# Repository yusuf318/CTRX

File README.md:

# CTRX
Yeniay Control Telemetry Project

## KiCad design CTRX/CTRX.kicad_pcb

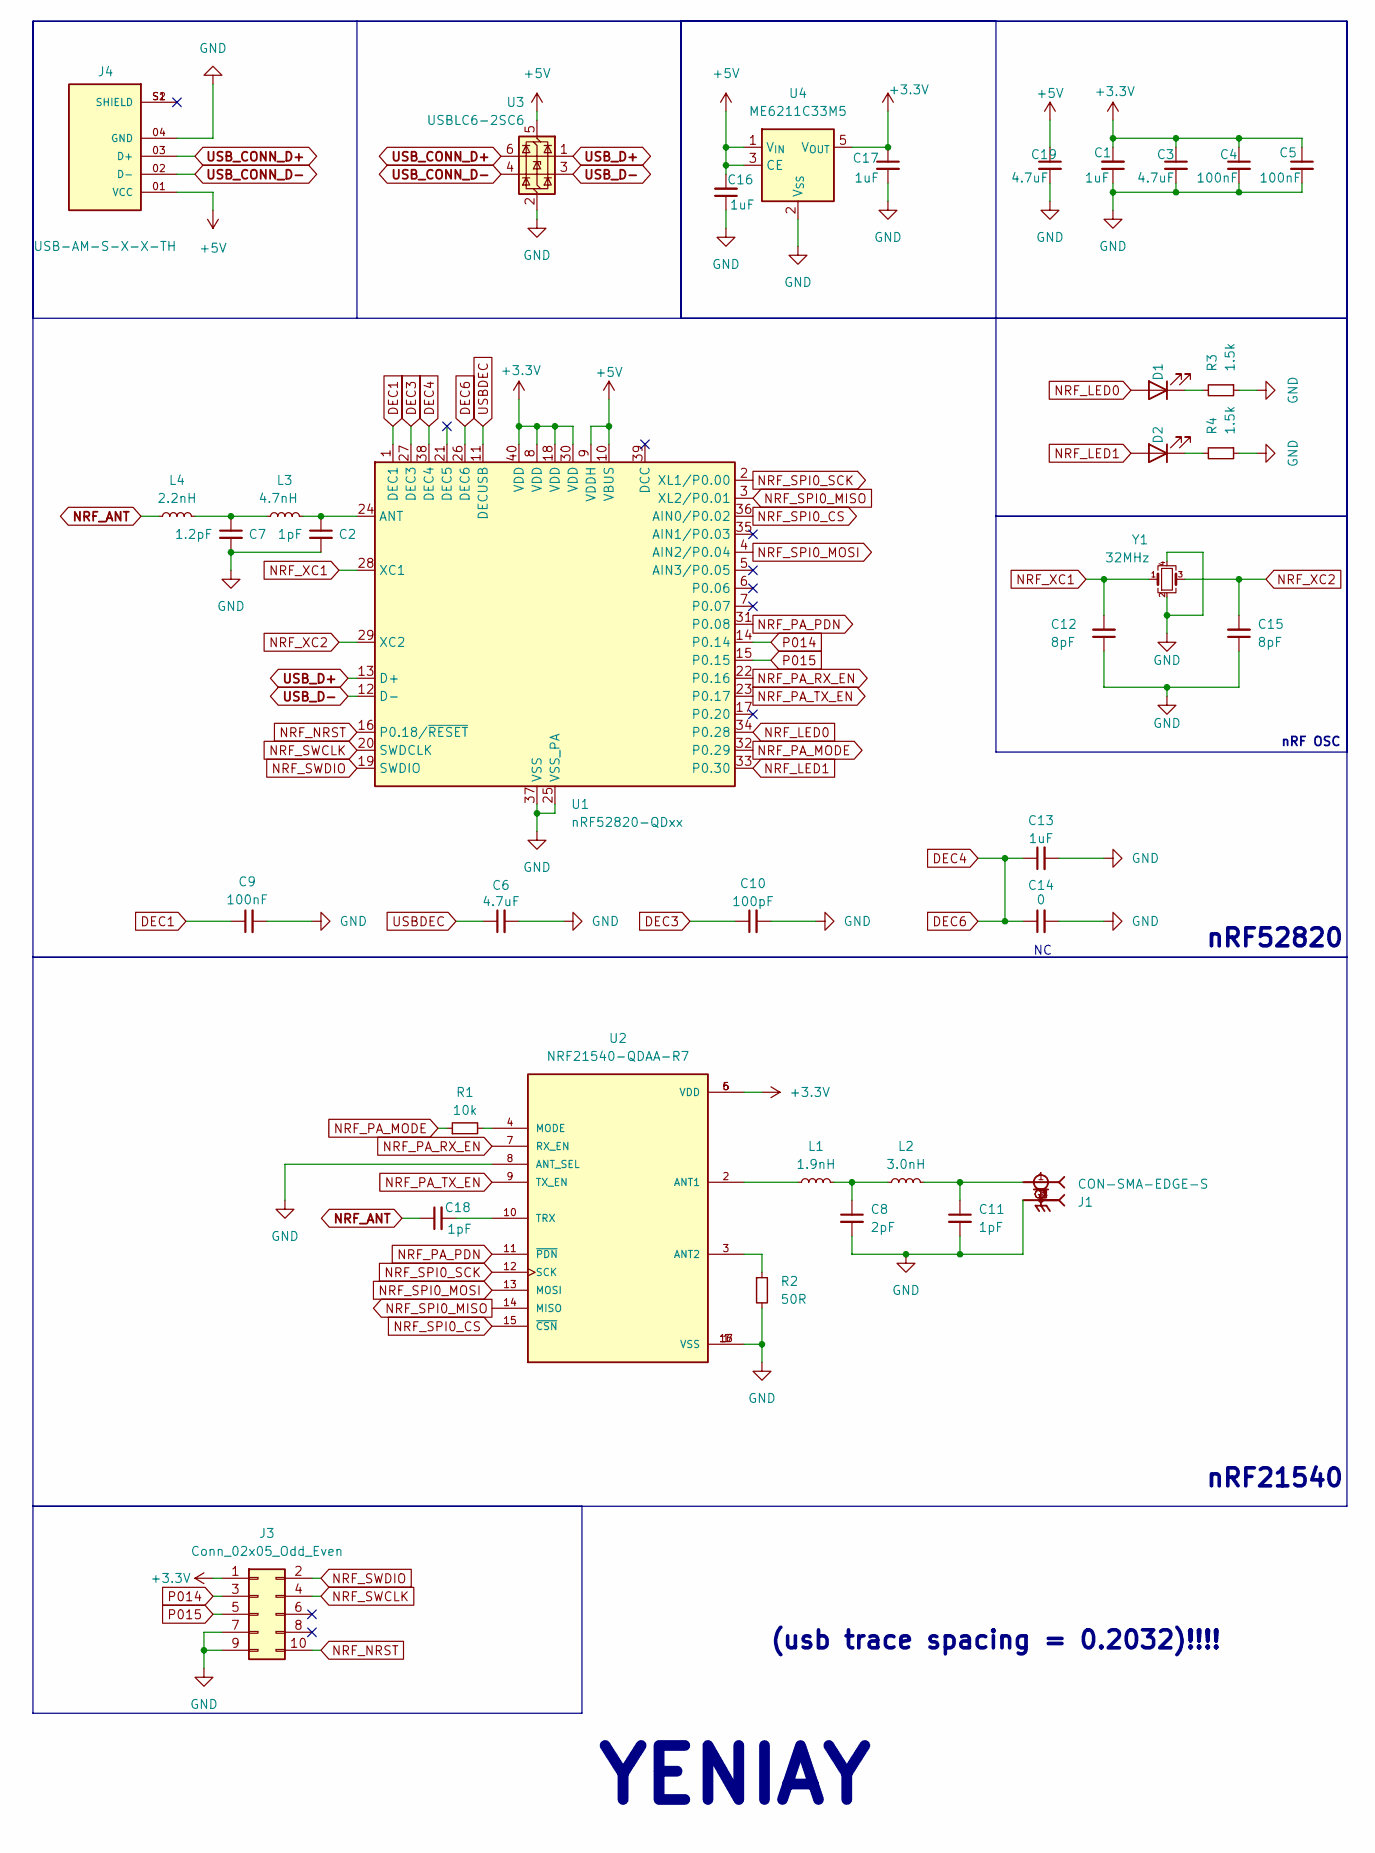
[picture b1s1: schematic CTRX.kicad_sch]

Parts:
C1, C13, C16, C17: 1uF; C_0402_1005Metric
C2, C11, C18: 1pF; C_0201_0603Metric
C3, C6, C19: 4.7uF; C_0603_1608Metric
C4, C5, C9: 100nF; C_0402_1005Metric
C7: 1.2pF; C_0201_0603Metric
C8: 2pF; C_0201_0603Metric
C10: 100pF; C_0402_1005Metric
C12, C15: 8pF; C_0402_1005Metric
C14: 0; C_0402_1005Metric
D1, D2: LED; LED_0805_2012Metric
J1: CON-SMA-EDGE-S; RFSOLUTIONS_CON-SMA-EDGE-S; PARTREV 1
J3: Conn_02x05_Odd_Even; IDC-Header_2x05_P2.54mm_Vertical
J4: USB-AM-S-X-X-TH; SAMTEC_USB-AM-S-X-X-TH; PARTREV U
L1: 1.9nH; L_0201_0603Metric
L2: 3.0nH; L_0201_0603Metric
L3: 4.7nH; L_0201_0603Metric
L4: 2.2nH; L_0201_0603Metric
R1: 10k; R_0402_1005Metric
R2: 50R; R_0402_1005Metric
R3, R4: 1.5k; R_0402_1005Metric
U1: nRF52820-QDxx; QFN-40-1EP_5x5mm_P0.4mm_EP3.6x3.6mm
U2: NRF21540-QDAA-R7; QFN65P400X400X95-17N; PARTREV 1.0
U3: USBLC6-2SC6; SOT-23-6
U4: ME6211C33M5; SOT-23-5
Y1: 32MHz; Crystal_SMD_3225-4Pin_3.2x2.5mm

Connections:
+3.3V: C1.2, C3.1, C4.1, C5.1, C17.1, J3.1, U1.8 (VDD), U1.18 (VDD), U1.30 (VDD), U1.40 (VDD), U2.5 (VDD), U2.6 (VDD), U4.5 (V_{OUT})
+5V: C16.2, C19.1, J4.01 (VCC), U1.9 (VDDH), U1.10 (VBUS), U3.5 (VBUS), U4.1 (V_{IN}), U4.3 (CE)
DEC1: C9.1, U1.1 (DEC1)
DEC3: C10.1, U1.27 (DEC3)
DEC4: C13.1, C14.1, U1.26 (DEC6), U1.38 (DEC4)
GND: C1.1, C2.2, C3.2, C4.2, C5.2, C6.2, C7.2, C8.2, C9.2, C10.2, C11.2, C12.1, C13.2, C14.2, C15.1, C16.1, C17.2, C19.2, J1.G1, J1.G2, J1.G3, J1.G4, J3.7, J3.9, J4.04 (GND), R2.2, R3.1, R4.1, U1.25 (VSS_PA), U1.37 (VSS), U1.41 (VSS), U2.1 (VSS), U2.8 (ANT_SEL), U2.16 (VSS), U2.17 (VSS), U3.2 (GND), U4.2 (V_{SS}), Y1.2, Y1.4
NRF_ANT: C18.1, L4.2
NRF_LED0: D1.2 (A), U1.34 (P0.28)
NRF_LED1: D2.2 (A), U1.33 (P0.30)
NRF_NRST: J3.10, U1.16 (P0.18/~RESET)
NRF_PA_MODE: R1.1, U1.32 (P0.29)
NRF_PA_PDN: U1.31 (P0.08), U2.11 (~PDN)
NRF_PA_RX_EN: U1.22 (P0.16), U2.7 (RX_EN)
NRF_PA_TX_EN: U1.23 (P0.17), U2.9 (TX_EN)
NRF_SPI0_CS: U1.36 (AIN0/P0.02), U2.15 (~CSN)
NRF_SPI0_MISO: U1.3 (XL2/P0.01), U2.14 (MISO)
NRF_SPI0_MOSI: U1.4 (AIN2/P0.04), U2.13 (MOSI)
NRF_SPI0_SCK: U1.2 (XL1/P0.00), U2.12 (SCK)
NRF_SWCLK: J3.4, U1.20 (SWDCLK)
NRF_SWDIO: J3.2, U1.19 (SWDIO)
NRF_XC1: C12.2, U1.28 (XC1), Y1.1
NRF_XC2: C15.2, U1.29 (XC2), Y1.3
unnamed: C7.1, L3.2, L4.1
unnamed: C8.1, L1.2, L2.1
unnamed: C11.1, J1.1, L2.2
unnamed: D1.1 (K), R3.2
unnamed: D2.1 (K), R4.2
unnamed: C2.1, L3.1, U1.24 (ANT)
unnamed: L1.1, U2.2 (ANT1)
unnamed: R2.1, U2.3 (ANT2)
unnamed: R1.2, U2.4 (MODE)
unnamed: C18.2, U2.10 (TRX)
P014: J3.3, U1.14 (P0.14)
P015: J3.5, U1.15 (P0.15)
USBDEC: C6.1, U1.11 (DECUSB)
USB_CONN_D+: J4.03 (D+), U3.6 (I/O1)
USB_CONN_D-: J4.02 (D-), U3.4 (I/O2)
USB_D+: U1.13 (D+), U3.1 (I/O1)
USB_D-: U1.12 (D-), U3.3 (I/O2)

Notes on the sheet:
nRF OSC
nRF21540
YENIAY
nRF52820
(usb trace spacing = 0.2032)!!!!

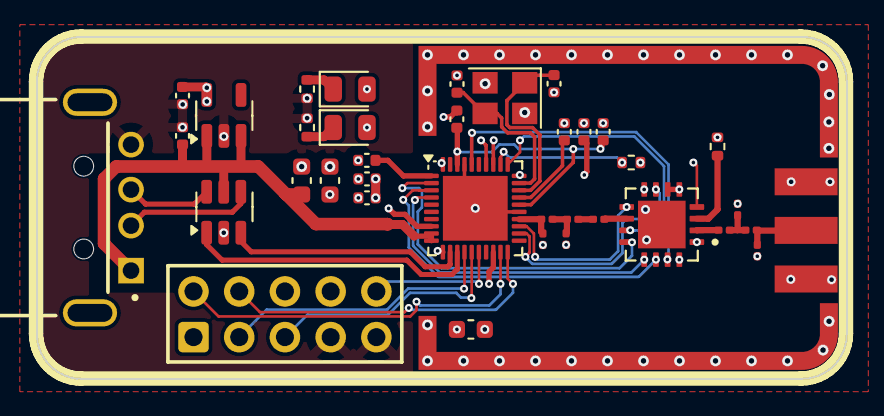
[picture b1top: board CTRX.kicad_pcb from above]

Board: 4 copper layers, 45.0 x 19.0 mm, 37 parts (0 on the bottom side), 39 nets.

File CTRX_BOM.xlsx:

Comment | Designator | Footprint | Part Number
1uF | C1, C13, C16, C17 | Capacitor_SMD:C_0402_1005Metric | C52923
1pF | C2, C11, C18 | Capacitor_SMD:C_0201_0603Metric | C88903
4.7uF | C3, C6, C19 | Capacitor_SMD:C_0603_1608Metric | C19666
100nF | C4, C5, C9 | Capacitor_SMD:C_0402_1005Metric | C1525
1.2pF | C7 | Capacitor_SMD:C_0201_0603Metric | C85895
2pF | C8 | Capacitor_SMD:C_0201_0603Metric | C505489
100pF | C10 | Capacitor_SMD:C_0402_1005Metric | C1546
8pF | C12, C15 | Capacitor_SMD:C_0402_1005Metric | C1864375
LED | D1 | LED_SMD:LED_0805_2012Metric | C2297
LED | D2 | LED_SMD:LED_0805_2012Metric | C2296
1.9nH | L1 | Inductor_SMD:L_0201_0603Metric | C206445
3.0nH | L2 | Inductor_SMD:L_0201_0603Metric | C86111
4.7nH | L3 | Inductor_SMD:L_0201_0603Metric | C86126
2.2nH | L4 | Inductor_SMD:L_0201_0603Metric | C1329438
10k | R1 | Resistor_SMD:R_0402_1005Metric | C25744
50R | R2 | Resistor_SMD:R_0402_1005Metric | C853312
1.5k | R3, R4 | Resistor_SMD:R_0402_1005Metric | C25867
nRF52820-QDxx | U1 | Package_DFN_QFN:QFN-40-1EP_5x5mm_P0.4mm_EP3.6x3.6mm | C3015612
NRF21540-QDAA-R7 | U2 | nRF21540:QFN65P400X400X95-17N | C5357827
USBLC6-2SC6 | U3 | Package_TO_SOT_SMD:SOT-23-6 | C7519
ME6211C33M5 | U4 | Package_TO_SOT_SMD:SOT-23-5 | C82942
32MHz | Y1 | Crystal:Crystal_SMD_3225-4Pin_3.2x2.5mm | C426985

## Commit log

2025-04-20 Start page settings.
2025-04-20 Selecting and adding component
2025-04-21 Scheme drawing.
2025-04-25 SPI3 pinleri kaldirildi, D+/D- baglantilari yapildi, NC pinler isaretlendi, C12/C15 12pF yapildi, dec kapasitorleri konumlandirildi, (2x5) debug connector ve ME6211 regulator eklendi.
2025-05-04 Pin baglantilari duzenlendi, C12/C15 12pF yapildi, nrf anten pinine 1 pF kapasitor eklendi, 2x5 debug connector ve regulator eklendi.
2025-05-09 schematic upgraded
2025-05-10 schematic updated
2025-05-11 dxf added.
2025-05-11 sma edge added
2025-05-20 capacitor covers were changed 0201->0402, pcb drawing was started
2025-05-20 CTRX updated
2025-05-26 Placement refactor | Zones added
2025-05-27 antenna
2025-05-27 ready
2025-05-27 CTRX Order Ready
2025-05-28 ready to order.
2025-05-29 via correction
2025-05-29 CTRX Order V3 - VIA Update
